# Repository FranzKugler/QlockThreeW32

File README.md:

# QlockThreeW32

ESP32 firmware for a **word clock** — a grid of letters, backlit so that the
current time reads as a sentence. The display changes every five minutes; four
corner LEDs fill in the minutes in between.

```
ES IST FÜNF NACH ZWEI          IT IS FIVE PAST TWO
```

Ten languages and dialects, a configuration web interface served by the clock
itself, and firmware updates through the browser. No cloud, no app, no account
— everything the clock needs it carries, and it works on a network with no
internet access at all.

---

## What it does

- **Ten languages**: German (standard, Swabian, Bavarian, Saxon), Swiss German,
  English, French, Italian, Dutch, Spanish. Each has its own irregular grammar
  — French and Italian agree the hour, the German dialects differ on
  *viertel* / *dreiviertel*.
- **Configuration in the browser**, served from the clock. The interface
  switches its own language along with the clock's.
- **Colour** as hue, saturation and brightness, beside a live preview of the
  real face — the lit letters are read back out of the clock's own frame
  buffer, not guessed at in the browser.
- **Automatic brightness** from an ambient light sensor, on a curve the clock
  learns from the way you use the slider — and, on a calibrated clock,
  **colour-aware**: the same setting emits far less light in deep blue than
  in green, and the automatic knows it. There is no "remember this" button.
- **Time from NTP**, with a region/place picker over both daylight-saving
  changeover rules, which stay editable by hand underneath.
- **Firmware and interface updates** from the browser, or automatically from a
  release channel.
- **Expert mode** — a password in front of the update, debug and storage tabs.
- A few debug displays: seconds counter, LED test pattern.

## Hardware

| | |
|---|---|
| Controller | Seeed XIAO ESP32-S3 **Plus** (16 MB flash) |
| LEDs | 114 × WS2812B on one strip, data on GPIO 4 |
| Layout | 11 × 10 letters = 110, plus 4 corner LEDs |
| Light sensor | ams **TSL2591** (0x29) or Vishay **VEML7700** (0x10) on I²C, SDA/SCL default to GPIO 5/6 — optional |

The strip starts at the **bottom right** letter, meanders left, then up one row
and back to the right, and ends at the **top right**. The four corner LEDs
follow it, in the order bottom right, top right, top left, bottom left.

```
index 0    bottom right   (the R of the German panel)
index 109  top right      (the F)
110 … 113  the corners
```

> `LedDriverWS2812FastLED::physicalFor(row, col)` is the only place that
> computes this, and the `/lab` interface can check any claim about it against
> the strip in seconds. Which frame buffer *row* is which corner is a separate
> question and lives at `Renderer::setCorners` — the path there goes through
> two remappings that partly cancel, and it was settled by watching a clock
> rather than by reading code.

**Either light sensor works, and the choice is made at run time** — the firmware
tries each in turn at boot and keeps the first that answers, so one build
serves every clock and a chip swapped on the bench needs no rebuild. The
TSL2591 is asked first: the two do not share an address, so a clock carrying
both answers twice, and the more sensitive one is the one to keep. With no
sensor fitted, the automatic hides itself rather than offering a switch that
does nothing.

The board and the case are in [`hardware/`](hardware/) — a KiCad project and an
OpenSCAD model. The letter mask is **not** drawn by hand: `scripts/panels.py`
reads the ten rows out of the firmware's own language files and writes
`panels.scad`, so the sheet that gets milled and the words the clock lights
cannot drift apart.

Earlier revisions supported other boards and LED drivers; the project has since
been consolidated onto this single target.

## Building

Two halves are built separately: the firmware, and the web interface that is
flashed into the clock's filesystem.

```sh
# web interface -> data/
npm install
npm run build

# firmware
pio run                  # build
pio run -t upload        # flash the firmware
pio run -t uploadfs      # flash data/ as the filesystem image
```

Both have to be flashed once over USB. After that, updates can go through the
browser.

> The board definition in PlatformIO describes the 8 MB XIAO ESP32-S3. This is
> the Plus with 16 MB, so [`platformio.ini`](platformio.ini) overrides the
> flash size and points at [`partitions.csv`](partitions.csv): two 6.5 MB OTA
> slots and a 3.5 MB filesystem.

### Credentials

Copy [`src/Secrets.example.h`](src/Secrets.example.h) to `src/Secrets.h` and
put in your own values — it is not in version control. The build works without
it, it just leaves network flashing via espota unprotected and says so with a
compiler warning.

## First start

With no WiFi configured the clock opens an access point called
**QlockThreeW32**. Connect to it and a captive portal asks for the network.
Afterwards the clock is reachable at **http://qlockthreew32.local** or by its
address in the network.

The clock can be renamed in the WLAN tab, which changes all six places the name
appears — mDNS, the DHCP name the router lists, the setup access point, the
espota target, the RemoteDebug host and the heading of the interface. It
restarts to do it, and says so.

Four tabs are open to anyone on the network:

| Tab | |
|---|---|
| Display | operating mode, language, corner LED direction and colour |
| Colour | hue, saturation, brightness, the automatic, and a preview of the face |
| Time zone | NTP server, a region/place picker, and both changeover rules |
| WLAN | status, scan, switching networks, renaming the clock |

Switching networks is deliberately careful: the clock tries the new
credentials, and if they do not come up within twenty seconds it returns to the
previous network by itself, so a typo cannot lock you out.

## Expert mode

Three more tabs — **Update**, **Debug** and **Storage** — are behind a
password, because flashing the clock, reading its log and rummaging through its
filesystem are not things every guest on the network should be able to do.

**The way in is the address bar: `http://<clock>/#expert`.** There is no chip
in the tab row, on purpose; a visible one would only invite guessing.

- A clock that has never been given a password takes the first one offered, and
  keeps it. Until then it is exactly as open as every clock was before this
  existed.
- It is a **mode, not a login**: one flag in NVS, so the password crosses the
  wire once instead of on every poll of the log. While unlocked, nothing is
  protected — hence the visible "lock again" button.
- **The way back from a forgotten password is the plug.** The enrolment can be
  cleared within five minutes of a *power-on* reset, which a restart from the
  clock's own update tab does not count as. Anyone who can pull the plug can
  read the flash over USB anyway, so this admits what is already true rather
  than pretending otherwise.
- Five wrong answers stop the endpoint for five minutes.

What it is worth: it keeps out someone who joins the network and goes looking.
It does not keep out someone watching the traffic — there is no TLS on the
clock — and it does not keep out anyone holding it.

Once unlocked:

| Tab | |
|---|---|
| Update | installed versions, browser upload, release channel and automatic installs |
| Debug | uptime, reset reason, heap, and the clock's last 200 log lines |
| Storage | a file explorer over LittleFS, and over NVS drawn as a tree |

### The lab interface

`/lab/*` hands a script direct control of every pixel and of the light sensor —
raw colours, no gamma, no smoothing, and a whole measurement series in one
request. [`scripts/lab.py`](scripts/lab.py) is the client:

```sh
python scripts/lab.py <address> find   # which cell is the light sensor in
python scripts/lab.py <address> ir     # does the infrared channel see the room
python scripts/lab.py <address> map    # coupling from every cell to the sensor
```

It is there because a word clock whose sensor can see its own face cannot
regulate on it, and how badly is a question of geometry that differs from clock
to clock. On the first clock it ran on it found the sensor in four minutes,
behind an unused filler letter three rows from the bottom.

Behind expert mode, and it never touches a setting: the mode it uses cannot be
stored, cannot be picked in the display tab, and ends with a restart.

Two more screens have no chip either. `#luminance` draws what the automatic
brightness has learned — deliberately *outside* expert mode, since there is no
secret in a brightness curve. `#expert` is the one above.

## Automatic brightness

Switch it on in the colour tab and the display follows the room. The curve is a
straight line in **log light**, because perception is roughly logarithmic and
the range to cover spans decades:

```
brightness = slope × log10(lux) + offset      held between 20 % and 100 %
```

**There is no "remember this" button, and that is the design.** Moving the
slider is the only signal anyone ever gives about whether the automatic got it
right, so the nudge *is* the calibration:

1. Move the brightness slider while the automatic is on. The automatic steps
   aside at once — nobody wants the clock arguing back mid-drag.
2. Ten seconds after the last move, the clock keeps the pair *(light now,
   brightness asked for)* and fits a new line through everything it has kept.

The switch keeps saying "automatic" throughout, because it still is: it is
being taught, not turned off. The timer is in the firmware, so closing the tab
mid-adjustment does not lose the point.

Ten points are kept, in NVS. A new one **replaces a near neighbour** rather
than joining the queue, or ten corrections made in one evening would push the
one daylight point out and collapse the line onto a single lighting condition.
If the points sit too close together to say anything about steepness, only the
level is re-fitted and the slope stands. A slope that would make a darker room
brighter is refused outright.

The reset button in the colour tab throws it all away and restores a cautious
default line.

### Colour-aware, on a calibrated clock

That single line is the fallback. A clock shipped with a measured optical
profile knows that a percentage is not an amount of light — the same setting
emits far less in deep blue than in the green this clock normally shows — and
regulates on a small model of the diffuser and LEDs instead: one line shared
by every colour, plus how each hue departs from it. Nudging the slider still
teaches it, now per colour, and a taught correction only overrides the factory
measurement where it actually disagrees with it — elsewhere the factory
number keeps speaking for itself, which is why a handful of evening
corrections in one colour do not retune the whole curve.

`#luminance` — reachable without unlocking expert mode, since there is no
secret in a brightness curve — draws the model as an interactive 3D surface:
hue running round, ambient light out from the centre (logarithmically,
brighter towards the middle), brightness as the height, with every taught
correction marked on it. A collapsible "fit parameters" section beside it has
the numbers themselves, for anyone curious.

## The two stores

The clock keeps things in two places, and the difference decides what survives
an update:

- **LittleFS**, 3.5 MB — the web interface, the timezone list, the icons. A
  filesystem update **overwrites it whole**.
- **NVS** — the settings, the expert password, the brightness curve. An update
  leaves it **untouched**, which is exactly why they live there.

The **Storage** tab shows both. NVS is not a filesystem and is drawn as one
anyway: namespaces as folders, keys as files, `.json` or `.bin` depending on
what the value turns out to be. Files can be downloaded, uploaded and edited in
place, JSON laid out on the way in and written back compact. Right-click, or
press and hold on a touch screen, for the menu.

Two things it will not do. The expert password hash is listed but never handed
out — it is the one secret whose leak would outlive the unlock that leaked it.
And deleting is not recursive, because a file explorer that empties a tree on
one click is how the web interface gets deleted by someone who meant to tidy
up.

> Clearing NVS resets the clock to defaults. Reflashing the filesystem no
> longer does.

## Flashing a blank chip

**[franzkugler.github.io/QlockThreeW32](https://franzkugler.github.io/QlockThreeW32/)**
flashes a factory-fresh Seeed XIAO ESP32-S3 Plus straight from Chrome, Edge or
Opera — no PlatformIO, no Python, nothing to install. It writes the whole
chip (bootloader, partition table, firmware and the configuration interface)
from whatever the latest stable release is, using
[ESP Web Tools](https://esphome.github.io/esp-web-tools/) over the Web Serial
API. Once a clock is running this firmware, updates go through its own
**Update** tab instead — see the next section.

The page is [`docs/`](docs/) in this repository, published as a GitHub Pages
site by [the release workflow](.github/workflows/release.yml) on every stable
release; see [`CLAUDE.md`](CLAUDE.md) for why it cannot simply point at the
release's own download URLs.

## Updating over the air

There are two images, and they are independent: `firmware.bin` (the program)
and `littlefs.bin` (the web interface). Changing the interface and only
flashing the firmware leaves the old interface in place.

Ready-built images come from
[the releases page](https://github.com/FranzKugler/QlockThreeW32/releases), in
two channels:

- **stable** — tagged versions, built from a `v*` tag.
- **edge** — a rolling build of the latest commit on `main`, replaced on every
  push. Untested by definition.

The clock can poll its channel by itself and install what it finds. Automatic
installs are off by default and only ever run between 02:00 and 05:00 local, so
the face never goes dark in the evening.

Locally the images are produced by `pio run` and `pio run -t buildfs` in
`.pio/build/seeed_xiao_esp32s3/`.

Upload either image in the **Update** tab — the clock recognises which is which
from the image itself (ESP32 program images start with the magic byte `0xE9`)
and picks the right partition.

The checksum is verified before the boot partition is switched, so an
interrupted upload does no harm: the clock simply keeps running the version it
has. There is no automatic rollback for an image that flashes correctly but
then crashes — that case needs a USB cable.

**The update endpoints are behind expert mode**, along with the log and the
storage tab. They were open by design while none of them existed as a web page.

## Layout of the repository

```
src/            firmware (PlatformIO / Arduino-ESP32)
  Renderer.*      hour/minute -> which words light up, no hardware involved
  languages/      one file per language: its letters, its words, its grammar
  LedDriver*      WS2812B output, colour and brightness
  LightSensor.*   TSL2591 / VEML7700 behind one interface, sampled on core 0
  Luminance.*     the brightness curve, and how it is learned
  FactoryProfile.*    the colour-aware model, as pure arithmetic
  FactoryLuminance.*  loads and validates the measured profile from LittleFS
  ResidualStore.*     what an owner has taught it, refit online against the profile
  Settings.*      persistence in NVS
  WebRoutes.*     the HTTP handlers; OtaUpdate, FileRoutes, NvsRoutes beside it
web/            configuration interface (Svelte 5 + Vite), built into data/
hardware/       KiCad project, and the OpenSCAD case and letter mask
scripts/        generators: the letter mask, the timezone list, the app icons
server.js       mock of the clock's REST API, for developing the UI without hardware
```

Everything in `scripts/` writes files that are **committed**, so neither a
build nor a 3D print needs Python. Edit the generator, never its output.

For UI work, run the mock and the dev server side by side — the interface then
behaves as it does on the device, on a desktop browser:

```sh
npm run mock     # REST API on :8080
npm run dev      # Vite with hot reload on :5173
```

[`CLAUDE.md`](CLAUDE.md) goes into the architecture in more detail.

## Origins

This is a long-running hobby project, and not the beginning of the story. It
descends from **Qlockthree** by *Christian Aschoff* — firmware for a
self-built QLOCKTWO-style clock, written for the Arduino/ATmega328 from
November 2011 onwards and maintained through version 3.4.9. Much of the
rendering code here is still his, as the file headers record.

- Project and downloads: <http://www.christians-bastel-laden.de/DOWNLOADS/index.html>
- Shop and build instructions: <http://www.christians-bastel-laden.de/>

The upstream firmware is not on GitHub itself; it is published as ZIP archives
on that page. Several people have mirrored and continued it, among them
[bracci/Qlockthree](https://github.com/bracci/Qlockthree),
[schwabe/qlockthree](https://github.com/schwabe/qlockthree) and
[cactus-online/Qlockthree](https://github.com/cactus-online/Qlockthree).
[bracci/QlockWiFive](https://github.com/bracci/QlockWiFive) and
[ch570512/Qlockwork](https://github.com/ch570512/Qlockwork) are separate ESP
firmwares for the same hardware idea.

Beyond that, the Swiss German variant goes back to *Thomas Schuler* and the
Dutch one to *Rudolf Klimesch*.

This repository takes that lineage to an ESP32-S3, and adds the web interface,
the WiFi handling and the over-the-air updates.

## License

**CC BY-NC-SA 3.0** — Attribution, NonCommercial, ShareAlike. See
[`LICENSE`](LICENSE).

This is inherited, not chosen: Christian Aschoff puts the original firmware
under CC BY-NC-SA 3.0, and the ShareAlike term carries over to anything built
on it. In short — keep the attributions, do not use it commercially, and pass
derivatives on under the same terms.

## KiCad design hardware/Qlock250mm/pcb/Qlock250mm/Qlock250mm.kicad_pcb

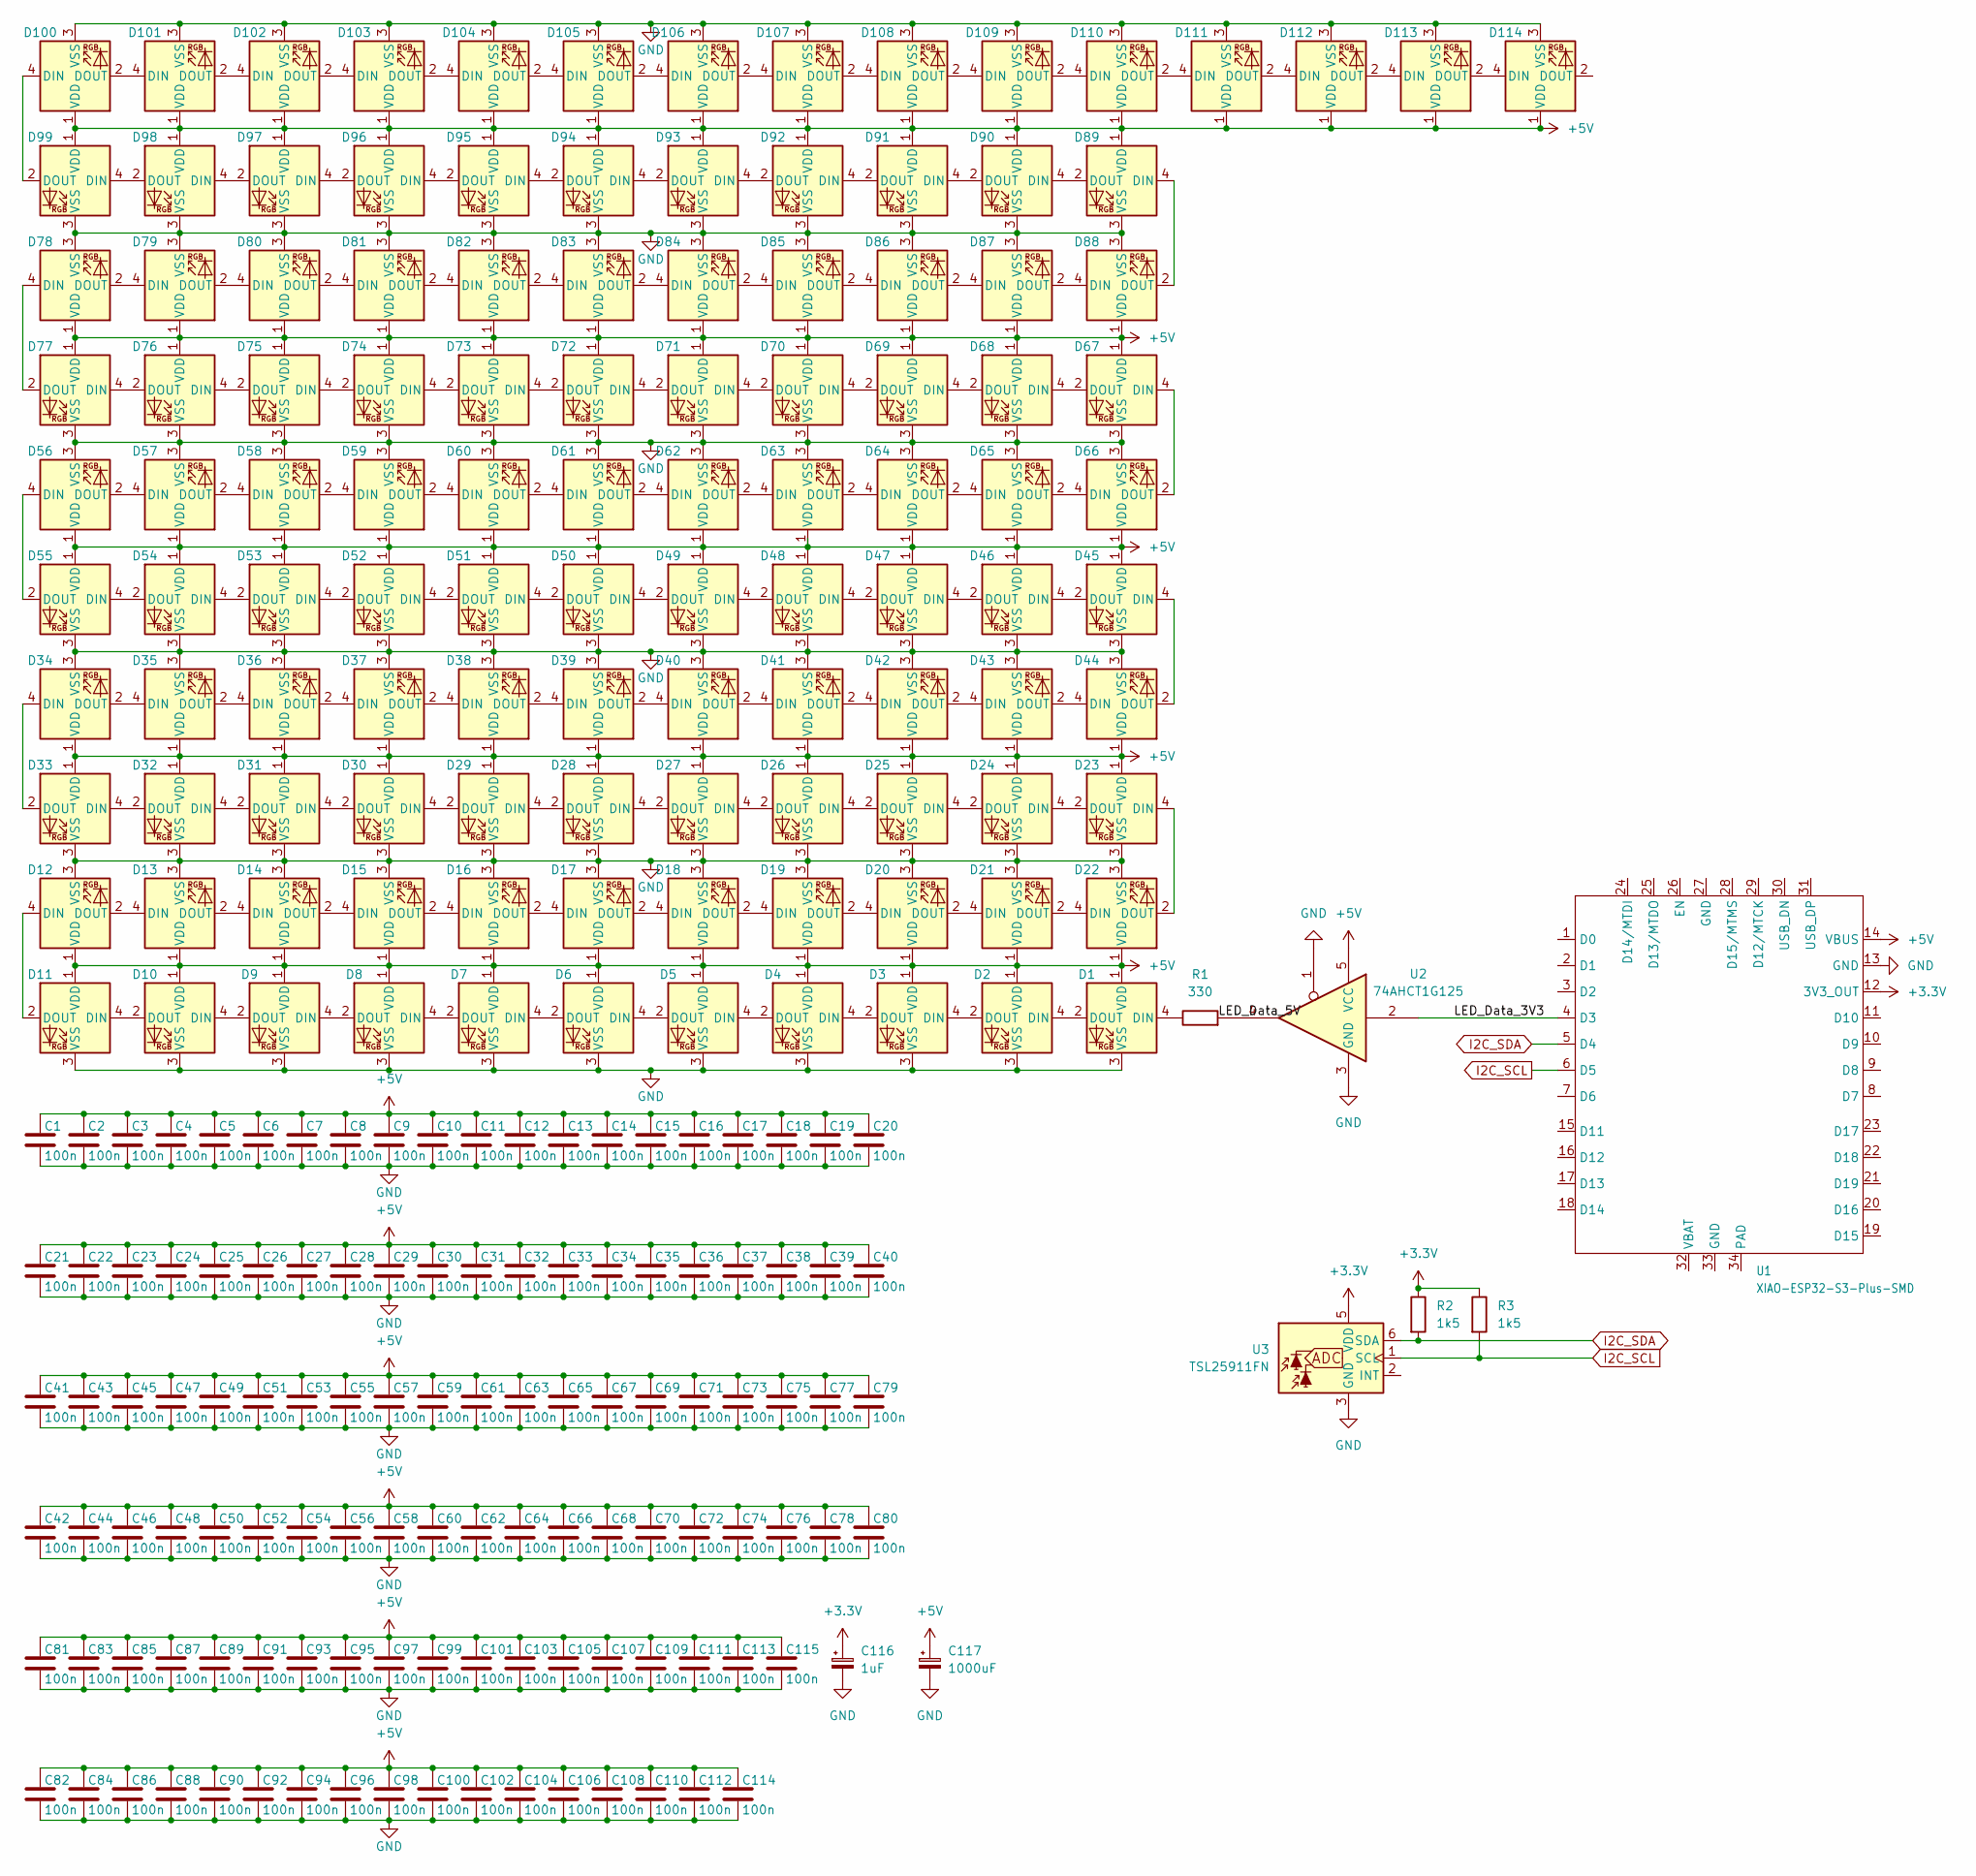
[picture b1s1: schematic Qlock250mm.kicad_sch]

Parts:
C1, C2, C3, C4, C5, C6, C7, C8, C9, C10, C11, C12, C13, C14, C15, C16, C17, C18, C19, C20, C21, C22, C23, C24, C25, C26, C27, C28, C29, C30, C31, C32, C33, C34, C35, C36, C37, C38, C39, C40, C41, C42, C43, C44, C45, C46, C47, C48, C49, C50, C51, C52, C53, C54, C55, C56, C57, C58, C59, C60, C61, C62, C63, C64, C65, C66, C67, C68, C69, C70, C71, C72, C73, C74, C75, C76, C77, C78, C79, C80, C81, C82, C83, C84, C85, C86, C87, C88, C89, C90, C91, C92, C93, C94, C95, C96, C97, C98, C99, C100, C101, C102, C103, C104, C105, C106, C107, C108, C109, C110, C111, C112, C113, C114, C115: 100n; C_0603_1608Metric; LCSC Part # C1588
C116: 1uF; C_0603_1608Metric; LCSC Part # C15849
C117: 1000uF; CP_Elec_10x10; LCSC Part # C249844
D1, D2, D3, D4, D5, D6, D7, D8, D9, D10, D11, D12, D13, D14, D15, D16, D17, D18, D19, D20, D21, D22, D23, D24, D25, D26, D27, D28, D29, D30, D31, D32, D33, D34, D35, D36, D37, D38, D39, D40, D41, D42, D43, D44, D45, D46, D47, D48, D49, D50, D51, D52, D53, D54, D55, D56, D57, D58, D59, D60, D61, D62, D63, D64, D65, D66, D67, D68, D69, D70, D71, D72, D73, D74, D75, D76, D77, D78, D79, D80, D81, D82, D83, D84, D85, D86, D87, D88, D89, D90, D91, D92, D93, D94, D95, D96, D97, D98, D99, D100, D101, D102, D103, D104, D105, D106, D107, D108, D109, D110, D111, D112, D113, D114: WS2812B; LED_WS2812B_PLCC4_5.0x5.0mm_P3.2mm; LCSC Part # C2843785
R1: 330; R_0402_1005Metric; LCSC Part # C25104
R2, R3: 1k5; R_0402_1005Metric; LCSC Part # C25867
U1: XIAO-ESP32-S3-Plus-SMD
U2: 74AHCT1G125; SOT-23-5; LCSC Part # C7484
U3: TSL25911FN; AMS_TSL25911FN; LCSC Part # C176812

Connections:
+3.3V: C116.1, R2.1, R3.1, U1.12 (3V3_OUT), U3.5 (VDD)
+5V: C1.1, C2.1, C3.1, C4.1, C5.1, C6.1, C7.1, C8.1, C9.1, C10.1, C11.1, C12.1, C13.1, C14.1, C15.1, C16.1, C17.1, C18.1, C19.1, C20.1, C21.1, C22.1, C23.1, C24.1, C25.1, C26.1, C27.1, C28.1, C29.1, C30.1, C31.1, C32.1, C33.1, C34.1, C35.1, C36.1, C37.1, C38.1, C39.1, C40.1, C41.1, C42.1, C43.1, C44.1, C45.1, C46.1, C47.1, C48.1, C49.1, C50.1, C51.1, C52.1, C53.1, C54.1, C55.1, C56.1, C57.1, C58.1, C59.1, C60.1, C61.1, C62.1, C63.1, C64.1, C65.1, C66.1, C67.1, C68.1, C69.1, C70.1, C71.1, C72.1, C73.1, C74.1, C75.1, C76.1, C77.1, C78.1, C79.1, C80.1, C81.1, C82.1, C83.1, C84.1, C85.1, C86.1, C87.1, C88.1, C89.1, C90.1, C91.1, C92.1, C93.1, C94.1, C95.1, C96.1, C97.1, C98.1, C99.1, C100.1, C101.1, C102.1, C103.1, C104.1, C105.1, C106.1, C107.1, C108.1, C109.1, C110.1, C111.1, C112.1, C113.1, C114.1, C115.1, C117.1, D1.1 (VDD), D2.1 (VDD), D3.1 (VDD), D4.1 (VDD), D5.1 (VDD), D6.1 (VDD), D7.1 (VDD), D8.1 (VDD), D9.1 (VDD), D10.1 (VDD), D11.1 (VDD), D12.1 (VDD), D13.1 (VDD), D14.1 (VDD), D15.1 (VDD), D16.1 (VDD), D17.1 (VDD), D18.1 (VDD), D19.1 (VDD), D20.1 (VDD), D21.1 (VDD), D22.1 (VDD), D23.1 (VDD), D24.1 (VDD), D25.1 (VDD), D26.1 (VDD), D27.1 (VDD), D28.1 (VDD), D29.1 (VDD), D30.1 (VDD), D31.1 (VDD), D32.1 (VDD), D33.1 (VDD), D34.1 (VDD), D35.1 (VDD), D36.1 (VDD), D37.1 (VDD), D38.1 (VDD), D39.1 (VDD), D40.1 (VDD), D41.1 (VDD), D42.1 (VDD), D43.1 (VDD), D44.1 (VDD), D45.1 (VDD), D46.1 (VDD), D47.1 (VDD), D48.1 (VDD), D49.1 (VDD), D50.1 (VDD), D51.1 (VDD), D52.1 (VDD), D53.1 (VDD), D54.1 (VDD), D55.1 (VDD), D56.1 (VDD), D57.1 (VDD), D58.1 (VDD), D59.1 (VDD), D60.1 (VDD), D61.1 (VDD), D62.1 (VDD), D63.1 (VDD), D64.1 (VDD), D65.1 (VDD), D66.1 (VDD), D67.1 (VDD), D68.1 (VDD), D69.1 (VDD), D70.1 (VDD), D71.1 (VDD), D72.1 (VDD), D73.1 (VDD), D74.1 (VDD), D75.1 (VDD), D76.1 (VDD), D77.1 (VDD), D78.1 (VDD), D79.1 (VDD), D80.1 (VDD), D81.1 (VDD), D82.1 (VDD), D83.1 (VDD), D84.1 (VDD), D85.1 (VDD), D86.1 (VDD), D87.1 (VDD), D88.1 (VDD), D89.1 (VDD), D90.1 (VDD), D91.1 (VDD), D92.1 (VDD), D93.1 (VDD), D94.1 (VDD), D95.1 (VDD), D96.1 (VDD), D97.1 (VDD), D98.1 (VDD), D99.1 (VDD), D100.1 (VDD), D101.1 (VDD), D102.1 (VDD), D103.1 (VDD), D104.1 (VDD), D105.1 (VDD), D106.1 (VDD), D107.1 (VDD), D108.1 (VDD), D109.1 (VDD), D110.1 (VDD), D111.1 (VDD), D112.1 (VDD), D113.1 (VDD), D114.1 (VDD), U1.14 (VBUS), U2.5 (VCC)
/LED_Data_3V3: U1.4 (D3), U2.2
GND: C1.2, C2.2, C3.2, C4.2, C5.2, C6.2, C7.2, C8.2, C9.2, C10.2, C11.2, C12.2, C13.2, C14.2, C15.2, C16.2, C17.2, C18.2, C19.2, C20.2, C21.2, C22.2, C23.2, C24.2, C25.2, C26.2, C27.2, C28.2, C29.2, C30.2, C31.2, C32.2, C33.2, C34.2, C35.2, C36.2, C37.2, C38.2, C39.2, C40.2, C41.2, C42.2, C43.2, C44.2, C45.2, C46.2, C47.2, C48.2, C49.2, C50.2, C51.2, C52.2, C53.2, C54.2, C55.2, C56.2, C57.2, C58.2, C59.2, C60.2, C61.2, C62.2, C63.2, C64.2, C65.2, C66.2, C67.2, C68.2, C69.2, C70.2, C71.2, C72.2, C73.2, C74.2, C75.2, C76.2, C77.2, C78.2, C79.2, C80.2, C81.2, C82.2, C83.2, C84.2, C85.2, C86.2, C87.2, C88.2, C89.2, C90.2, C91.2, C92.2, C93.2, C94.2, C95.2, C96.2, C97.2, C98.2, C99.2, C100.2, C101.2, C102.2, C103.2, C104.2, C105.2, C106.2, C107.2, C108.2, C109.2, C110.2, C111.2, C112.2, C113.2, C114.2, C115.2, C116.2, C117.2, D1.3 (VSS), D2.3 (VSS), D3.3 (VSS), D4.3 (VSS), D5.3 (VSS), D6.3 (VSS), D7.3 (VSS), D8.3 (VSS), D9.3 (VSS), D10.3 (VSS), D11.3 (VSS), D12.3 (VSS), D13.3 (VSS), D14.3 (VSS), D15.3 (VSS), D16.3 (VSS), D17.3 (VSS), D18.3 (VSS), D19.3 (VSS), D20.3 (VSS), D21.3 (VSS), D22.3 (VSS), D23.3 (VSS), D24.3 (VSS), D25.3 (VSS), D26.3 (VSS), D27.3 (VSS), D28.3 (VSS), D29.3 (VSS), D30.3 (VSS), D31.3 (VSS), D32.3 (VSS), D33.3 (VSS), D34.3 (VSS), D35.3 (VSS), D36.3 (VSS), D37.3 (VSS), D38.3 (VSS), D39.3 (VSS), D40.3 (VSS), D41.3 (VSS), D42.3 (VSS), D43.3 (VSS), D44.3 (VSS), D45.3 (VSS), D46.3 (VSS), D47.3 (VSS), D48.3 (VSS), D49.3 (VSS), D50.3 (VSS), D51.3 (VSS), D52.3 (VSS), D53.3 (VSS), D54.3 (VSS), D55.3 (VSS), D56.3 (VSS), D57.3 (VSS), D58.3 (VSS), D59.3 (VSS), D60.3 (VSS), D61.3 (VSS), D62.3 (VSS), D63.3 (VSS), D64.3 (VSS), D65.3 (VSS), D66.3 (VSS), D67.3 (VSS), D68.3 (VSS), D69.3 (VSS), D70.3 (VSS), D71.3 (VSS), D72.3 (VSS), D73.3 (VSS), D74.3 (VSS), D75.3 (VSS), D76.3 (VSS), D77.3 (VSS), D78.3 (VSS), D79.3 (VSS), D80.3 (VSS), D81.3 (VSS), D82.3 (VSS), D83.3 (VSS), D84.3 (VSS), D85.3 (VSS), D86.3 (VSS), D87.3 (VSS), D88.3 (VSS), D89.3 (VSS), D90.3 (VSS), D91.3 (VSS), D92.3 (VSS), D93.3 (VSS), D94.3 (VSS), D95.3 (VSS), D96.3 (VSS), D97.3 (VSS), D98.3 (VSS), D99.3 (VSS), D100.3 (VSS), D101.3 (VSS), D102.3 (VSS), D103.3 (VSS), D104.3 (VSS), D105.3 (VSS), D106.3 (VSS), D107.3 (VSS), D108.3 (VSS), D109.3 (VSS), D110.3 (VSS), D111.3 (VSS), D112.3 (VSS), D113.3 (VSS), D114.3 (VSS), U1.13 (GND), U2.1, U2.3 (GND), U3.3 (GND)
I2C_SCL: R3.2, U1.6 (D5), U3.1 (SCL)
I2C_SDA: R2.2, U1.5 (D4), U3.6 (SDA)
unnamed: D1.4 (DIN), R1.1
unnamed: D1.2 (DOUT), D2.4 (DIN)
unnamed: D2.2 (DOUT), D3.4 (DIN)
unnamed: D3.2 (DOUT), D4.4 (DIN)
unnamed: D4.2 (DOUT), D5.4 (DIN)
unnamed: D5.2 (DOUT), D6.4 (DIN)
unnamed: D6.2 (DOUT), D7.4 (DIN)
unnamed: D7.2 (DOUT), D8.4 (DIN)
unnamed: D8.2 (DOUT), D9.4 (DIN)
unnamed: D9.2 (DOUT), D10.4 (DIN)
unnamed: D10.2 (DOUT), D11.4 (DIN)
unnamed: D11.2 (DOUT), D12.4 (DIN)
unnamed: D12.2 (DOUT), D13.4 (DIN)
unnamed: D13.2 (DOUT), D14.4 (DIN)
unnamed: D14.2 (DOUT), D15.4 (DIN)
unnamed: D15.2 (DOUT), D16.4 (DIN)
unnamed: D16.2 (DOUT), D17.4 (DIN)
unnamed: D17.2 (DOUT), D18.4 (DIN)
unnamed: D18.2 (DOUT), D19.4 (DIN)
unnamed: D19.2 (DOUT), D20.4 (DIN)
unnamed: D20.2 (DOUT), D21.4 (DIN)
unnamed: D21.2 (DOUT), D22.4 (DIN)
unnamed: D22.2 (DOUT), D23.4 (DIN)
unnamed: D23.2 (DOUT), D24.4 (DIN)
unnamed: D24.2 (DOUT), D25.4 (DIN)
unnamed: D25.2 (DOUT), D26.4 (DIN)
unnamed: D26.2 (DOUT), D27.4 (DIN)
unnamed: D27.2 (DOUT), D28.4 (DIN)
unnamed: D28.2 (DOUT), D29.4 (DIN)
unnamed: D29.2 (DOUT), D30.4 (DIN)
unnamed: D30.2 (DOUT), D31.4 (DIN)
unnamed: D31.2 (DOUT), D32.4 (DIN)
unnamed: D32.2 (DOUT), D33.4 (DIN)
unnamed: D33.2 (DOUT), D34.4 (DIN)
unnamed: D34.2 (DOUT), D35.4 (DIN)
unnamed: D35.2 (DOUT), D36.4 (DIN)
unnamed: D36.2 (DOUT), D37.4 (DIN)
unnamed: D37.2 (DOUT), D38.4 (DIN)
unnamed: D38.2 (DOUT), D39.4 (DIN)
unnamed: D39.2 (DOUT), D40.4 (DIN)
unnamed: D40.2 (DOUT), D41.4 (DIN)
unnamed: D41.2 (DOUT), D42.4 (DIN)
unnamed: D42.2 (DOUT), D43.4 (DIN)
unnamed: D43.2 (DOUT), D44.4 (DIN)
unnamed: D44.2 (DOUT), D45.4 (DIN)
unnamed: D45.2 (DOUT), D46.4 (DIN)
unnamed: D46.2 (DOUT), D47.4 (DIN)
unnamed: D47.2 (DOUT), D48.4 (DIN)
unnamed: D48.2 (DOUT), D49.4 (DIN)
unnamed: D49.2 (DOUT), D50.4 (DIN)
unnamed: D50.2 (DOUT), D51.4 (DIN)
unnamed: D51.2 (DOUT), D52.4 (DIN)
unnamed: D52.2 (DOUT), D53.4 (DIN)
unnamed: D53.2 (DOUT), D54.4 (DIN)
unnamed: D54.2 (DOUT), D55.4 (DIN)
unnamed: D55.2 (DOUT), D56.4 (DIN)
unnamed: D56.2 (DOUT), D57.4 (DIN)
unnamed: D57.2 (DOUT), D58.4 (DIN)
unnamed: D58.2 (DOUT), D59.4 (DIN)
unnamed: D59.2 (DOUT), D60.4 (DIN)
unnamed: D60.2 (DOUT), D61.4 (DIN)
unnamed: D61.2 (DOUT), D62.4 (DIN)
unnamed: D62.2 (DOUT), D63.4 (DIN)
unnamed: D63.2 (DOUT), D64.4 (DIN)
unnamed: D64.2 (DOUT), D65.4 (DIN)
unnamed: D65.2 (DOUT), D66.4 (DIN)
unnamed: D66.2 (DOUT), D67.4 (DIN)
unnamed: D67.2 (DOUT), D68.4 (DIN)
unnamed: D68.2 (DOUT), D69.4 (DIN)
unnamed: D69.2 (DOUT), D70.4 (DIN)
unnamed: D70.2 (DOUT), D71.4 (DIN)
unnamed: D71.2 (DOUT), D72.4 (DIN)
unnamed: D72.2 (DOUT), D73.4 (DIN)
unnamed: D73.2 (DOUT), D74.4 (DIN)
unnamed: D74.2 (DOUT), D75.4 (DIN)
unnamed: D75.2 (DOUT), D76.4 (DIN)
unnamed: D76.2 (DOUT), D77.4 (DIN)
unnamed: D77.2 (DOUT), D78.4 (DIN)
unnamed: D78.2 (DOUT), D79.4 (DIN)
unnamed: D79.2 (DOUT), D80.4 (DIN)
unnamed: D80.2 (DOUT), D81.4 (DIN)
unnamed: D81.2 (DOUT), D82.4 (DIN)
unnamed: D82.2 (DOUT), D83.4 (DIN)
unnamed: D83.2 (DOUT), D84.4 (DIN)
unnamed: D84.2 (DOUT), D85.4 (DIN)
unnamed: D85.2 (DOUT), D86.4 (DIN)
unnamed: D86.2 (DOUT), D87.4 (DIN)
unnamed: D87.2 (DOUT), D88.4 (DIN)
unnamed: D88.2 (DOUT), D89.4 (DIN)
unnamed: D89.2 (DOUT), D90.4 (DIN)
unnamed: D90.2 (DOUT), D91.4 (DIN)
unnamed: D91.2 (DOUT), D92.4 (DIN)
unnamed: D92.2 (DOUT), D93.4 (DIN)
unnamed: D93.2 (DOUT), D94.4 (DIN)
unnamed: D94.2 (DOUT), D95.4 (DIN)
unnamed: D95.2 (DOUT), D96.4 (DIN)
unnamed: D96.2 (DOUT), D97.4 (DIN)
unnamed: D97.2 (DOUT), D98.4 (DIN)
unnamed: D98.2 (DOUT), D99.4 (DIN)
unnamed: D99.2 (DOUT), D100.4 (DIN)
unnamed: D100.2 (DOUT), D101.4 (DIN)
unnamed: D101.2 (DOUT), D102.4 (DIN)
unnamed: D102.2 (DOUT), D103.4 (DIN)
unnamed: D103.2 (DOUT), D104.4 (DIN)
unnamed: D104.2 (DOUT), D105.4 (DIN)
unnamed: D105.2 (DOUT), D106.4 (DIN)
unnamed: D106.2 (DOUT), D107.4 (DIN)
unnamed: D107.2 (DOUT), D108.4 (DIN)
unnamed: D108.2 (DOUT), D109.4 (DIN)
unnamed: D109.2 (DOUT), D110.4 (DIN)
unnamed: D110.2 (DOUT), D111.4 (DIN)
unnamed: D111.2 (DOUT), D112.4 (DIN)
unnamed: D112.2 (DOUT), D113.4 (DIN)
unnamed: D113.2 (DOUT), D114.4 (DIN)
unnamed: R1.2, U2.4

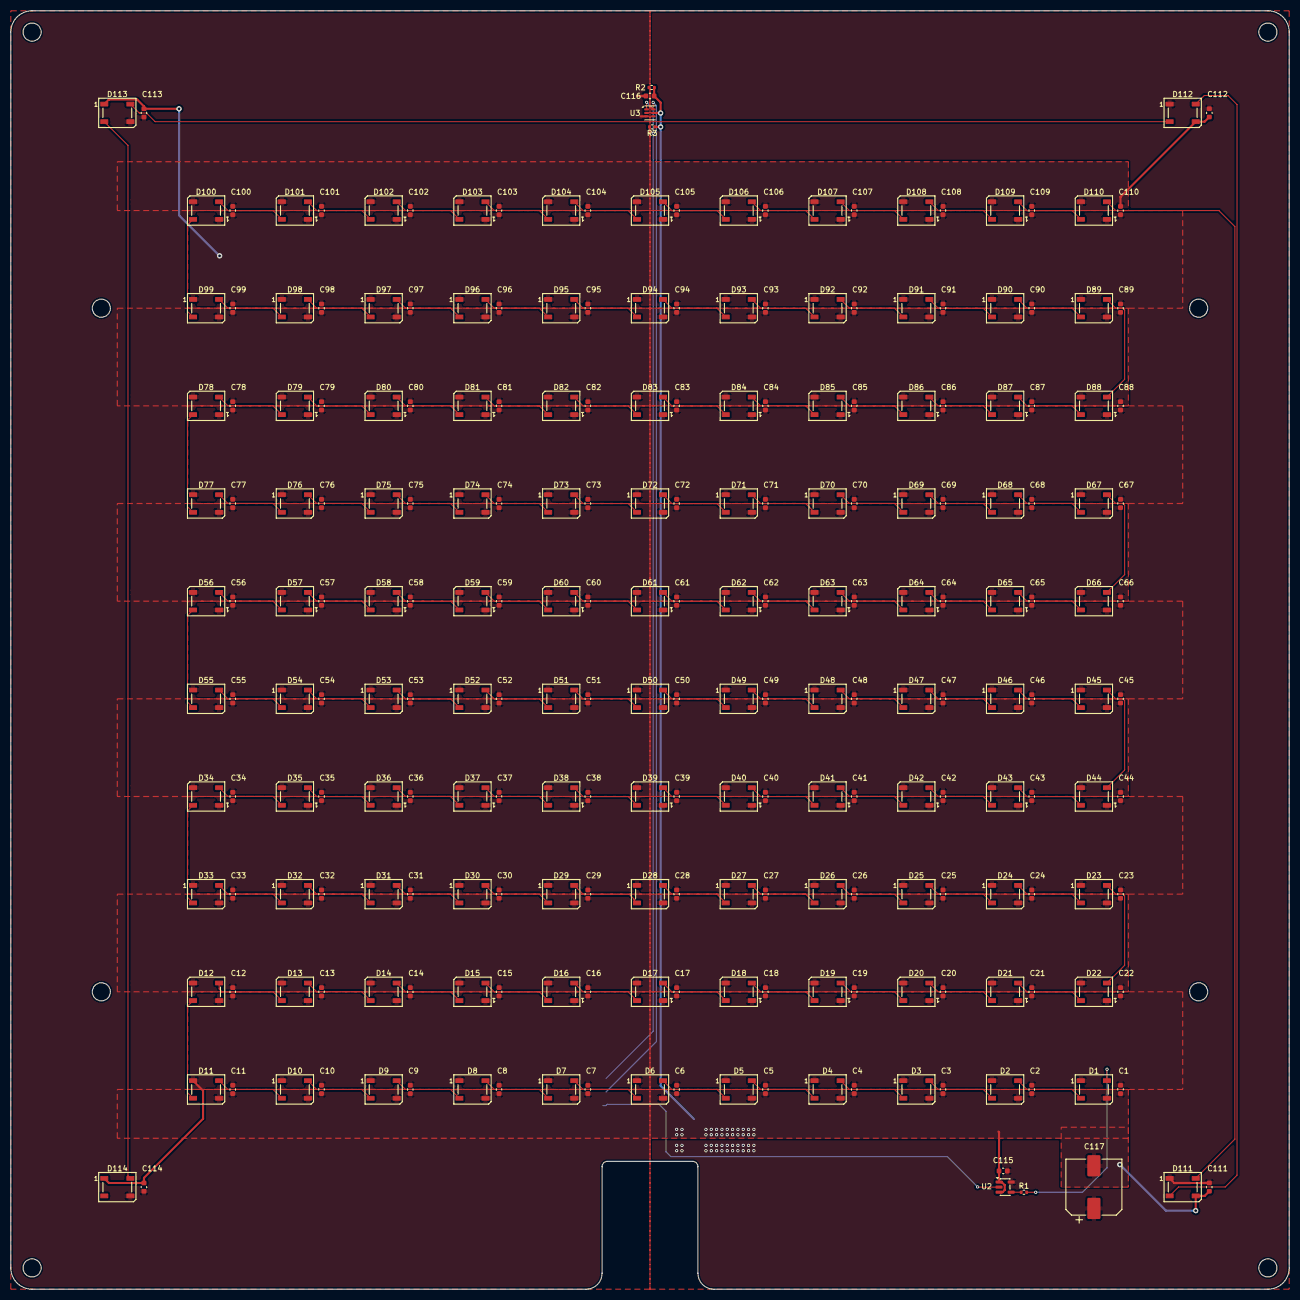
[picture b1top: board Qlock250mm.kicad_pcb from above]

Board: 2 copper layers, 240.0 x 240.0 mm, 237 parts (1 on the bottom side), 121 nets.
